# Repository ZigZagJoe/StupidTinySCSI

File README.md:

StupidTinySCSI
Derived from ZuliSCSI Pico OSHW.

This should be good but has not been 100% validated.

See below for orginal document.....

ZuluSCSI™ Pico Community Edition - Open Source Hardware
========================

This repository contains the KiCAD 7 schematic and PCB design files for the Pico-based ZuluSCSI™ SCSI to SD storage emulator, which is derived from the ZuluSCSI RP2040 board design. Firmware for ZuluSCSI is available at http://github.com/ZuluSCSI/ZuluSCSI-firmware.

This hardware design is licensed under the terms of the strongly reciprocal CERN OHL-S V2 license, which can be viewed in full at https://ohwr.org/cern_ohl_s_v2.txt and https://ohwr.org/cern_ohl_s_v2.pdf. 

ZuluSCSI™ is a registered trademark of Rabbit Hole Computing, and may not be used commercially without the express written consent of Rabbit Hole Computing. Individuals producing ZuluSCSI boards for personal use are hereby granted permission to use the ZuluSCSI trademark in a noncommercial capacity.

_Any_ use of the ZuluSCSI trademark in a **commercial** context requires prior written consent from Rabbit Hole Computing.

Firmware for ZuluSCSI is licensed under the GNU GPL Version 3, and can be found at https://github.com/zuluscsi/ZuluSCSI-firmware

Generating fabrication files
----------------------------

The component part numbers are stored in KiCAD schematic.
Manufacturing files, including assembly BOM, can be generated using [KiKit](https://github.com/yaqwsx/KiKit).

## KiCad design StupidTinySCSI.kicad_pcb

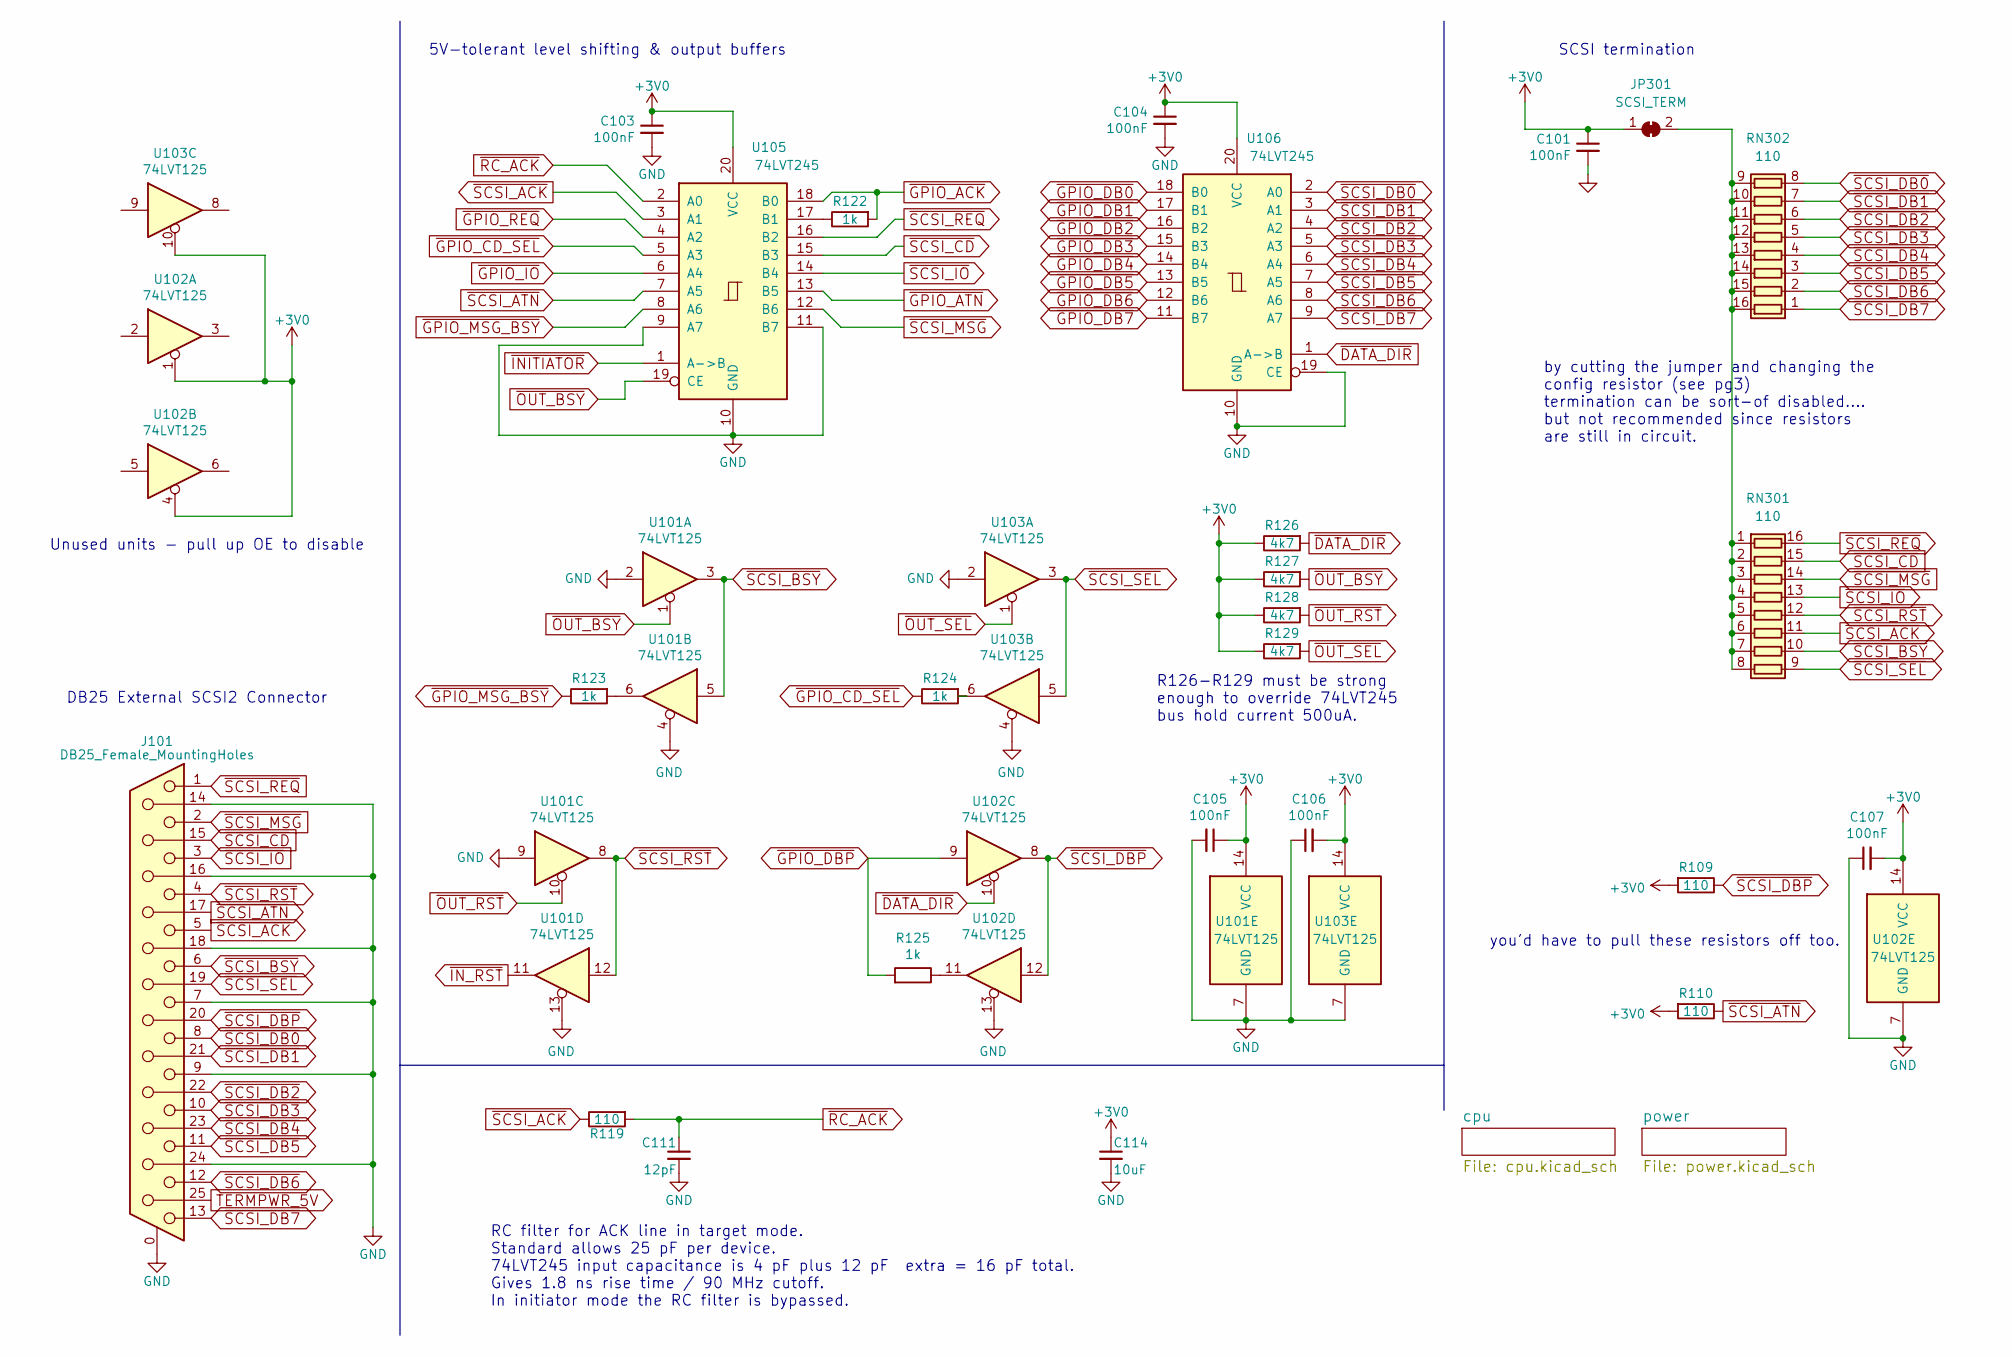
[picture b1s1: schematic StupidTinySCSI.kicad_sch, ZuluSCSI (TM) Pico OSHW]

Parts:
C101, C103, C104, C105, C106, C107: 100nF; C_0603_1608Metric; PartNumber CL10B104KB8NNWC; LCSC C14663
C111: 12pF; C_0603_1608Metric; PartNumber C0603C120J5GAC7867; LCSC C38523
C114: 10uF; C_0805_2012Metric; PartNumber CL21A106KPFNNNG; LCSC C15850
J101: DB25_Female_MountingHoles; DSUB-25_Female_Horizontal_P2.77x2.84mm_EdgePinOffset9.90mm_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; LCSC N/A
JP301: SCSI_TERM; SolderJumper-2_P1.3mm_Bridged_RoundedPad1.0x1.5mm
R109, R110, R119: 110; R_0603_1608Metric; PartNumber RC0603FR-07110RL; LCSC C22781
R122, R123, R124, R125: 1k; R_0603_1608Metric; PartNumber RC0603JR-071KL; LCSC C21190
R126, R127, R128, R129: 4k7; R_0603_1608Metric; PartNumber RC0603JR-074K7L; LCSC C23162
RN301, RN302: 110; R_Array_Convex_8x0602
U101, U102, U103: 74LVT125; SSOP_TSSOP-14_4.4x5mm_Pitch0.65mm_PCBWay-MaskClearance0.22mm; PartNumber 74LVTH125MTC; LCSC C7042
U105, U106: 74LVT245; SSOP_TSSOP-20_5.3x7.2mm_P0.65mm; PartNumber 74LVT245BBT20-13; LCSC C7057

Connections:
+3V0: C101.1, C103.1, C104.1, C105.1, C106.2, C107.2, C114.1, JP301.1 (A), R109.2, R110.2, R126.1, R127.1, R128.1, R129.1, U101.14 (VCC), U102.1, U102.4, U102.14 (VCC), U103.10, U103.14 (VCC), U105.20 (VCC), U106.20 (VCC); also elsewhere on the board
GND: C101.2, C103.2, C104.2, C105.2, C106.1, C107.1, C111.2, C114.2, J101.0 (PAD), J101.7, J101.9, J101.14, J101.16, J101.18, J101.24, U101.2, U101.4, U101.7 (GND), U101.9, U101.13, U102.7 (GND), U102.13, U103.2, U103.4, U103.7 (GND), U105.9 (A7), U105.10 (GND), U105.11 (B7), U106.10 (GND), U106.19 (CE); also elsewhere on the board
unnamed: JP301.2 (B), RN301.1 (R1.1), RN301.2 (R2.1), RN301.3 (R3.1), RN301.4 (R4.1), RN301.5 (R5.1), RN301.6 (R6.1), RN301.7 (R7.1), RN301.8 (R8.1), RN302.9 (R8.2), RN302.10 (R7.2), RN302.11 (R6.2), RN302.12 (R5.2), RN302.13 (R4.2), RN302.14 (R3.2), RN302.15 (R2.2), RN302.16 (R1.2)
unnamed: R123.2, U101.6
unnamed: R124.2, U103.6
unnamed: R125.1, U102.11
unnamed: R122.1, U105.17 (B1)
TERMPWR_5V: J101.25; also elsewhere on the board
~DATA_DIR: R126.2, U102.10, U106.1 (A->B); also elsewhere on the board
~DBGLOG: U105.4 (A2); also elsewhere on the board
~GPIO_ACK: R122.2, U105.18 (B0); also elsewhere on the board
~GPIO_ATN: U105.1 (A->B), U105.13 (B5); also elsewhere on the board
~GPIO_CD_SEL: R124.1, U105.5 (A3); also elsewhere on the board
~GPIO_DB0: U106.18 (B0); also elsewhere on the board
~GPIO_DB1: U106.17 (B1); also elsewhere on the board
~GPIO_DB2: U106.16 (B2); also elsewhere on the board
~GPIO_DB3: U106.15 (B3); also elsewhere on the board
~GPIO_DB4: U106.14 (B4); also elsewhere on the board
~GPIO_DB5: U106.13 (B5); also elsewhere on the board
~GPIO_DB6: U106.12 (B6); also elsewhere on the board
~GPIO_DB7: U106.11 (B7); also elsewhere on the board
~GPIO_DBP: R125.2, U102.9; also elsewhere on the board
~GPIO_IO: U105.6 (A4); also elsewhere on the board
~GPIO_MSG_BSY: R123.1, U105.8 (A6); also elsewhere on the board
~IN_RST: U101.11; also elsewhere on the board
~OUT_BSY: R127.2, U101.1, U105.19 (CE); also elsewhere on the board
~OUT_RST: R128.2, U101.10; also elsewhere on the board
~OUT_SEL: R129.2, U103.1; also elsewhere on the board
~RC_ACK: C111.1, R119.2, U105.2 (A0)
~SCSI_ACK: J101.5, R119.1, RN301.11 (R6.2), U105.3 (A1)
~SCSI_ATN: J101.17, R110.1, U105.7 (A5)
~SCSI_BSY: J101.6, RN301.10 (R7.2), U101.3, U101.5
~SCSI_CD: J101.15, RN301.15 (R2.2), U105.15 (B3)
~SCSI_DB0: J101.8, RN302.8 (R8.1), U106.2 (A0)
~SCSI_DB1: J101.21, RN302.7 (R7.1), U106.3 (A1)
~SCSI_DB2: J101.22, RN302.6 (R6.1), U106.4 (A2)
~SCSI_DB3: J101.10, RN302.5 (R5.1), U106.5 (A3)
~SCSI_DB4: J101.23, RN302.4 (R4.1), U106.6 (A4)
~SCSI_DB5: J101.11, RN302.3 (R3.1), U106.7 (A5)
~SCSI_DB6: J101.12, RN302.2 (R2.1), U106.8 (A6)
~SCSI_DB7: J101.13, RN302.1 (R1.1), U106.9 (A7)
~SCSI_DBP: J101.20, R109.1, U102.8, U102.12
~SCSI_IO: J101.3, RN301.13 (R4.2), U105.14 (B4)
~SCSI_MSG: J101.2, RN301.14 (R3.2), U105.12 (B6)
~SCSI_REQ: J101.1, RN301.16 (R1.2), U105.16 (B2)
~SCSI_RST: J101.4, RN301.12 (R5.2), U101.8, U101.12
~SCSI_SEL: J101.19, RN301.9 (R8.2), U103.3, U103.5

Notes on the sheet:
SCSI termination
R126-R129 must be strong enough to override 74LVT245 bus hold current 500uA.
5V-tolerant level shifting & output buffers
you'd have to pull these resistors off too.
by cutting the jumper and changing the config resistor (see pg3) termination can be sort-of disabled.... but not recommended since resistors are still in circuit.
Unused units - pull up OE to disable
DB25 External SCSI2 Connector
RC filter for ACK line in target mode. Standard allows 25 pF per device. 74LVT245 input capacitance is 4 pF plus 12 pF extra = 16 pF total. Gives 1.8 ns rise time / 90 MHz cutoff. In initiator mode the RC filter is bypassed.

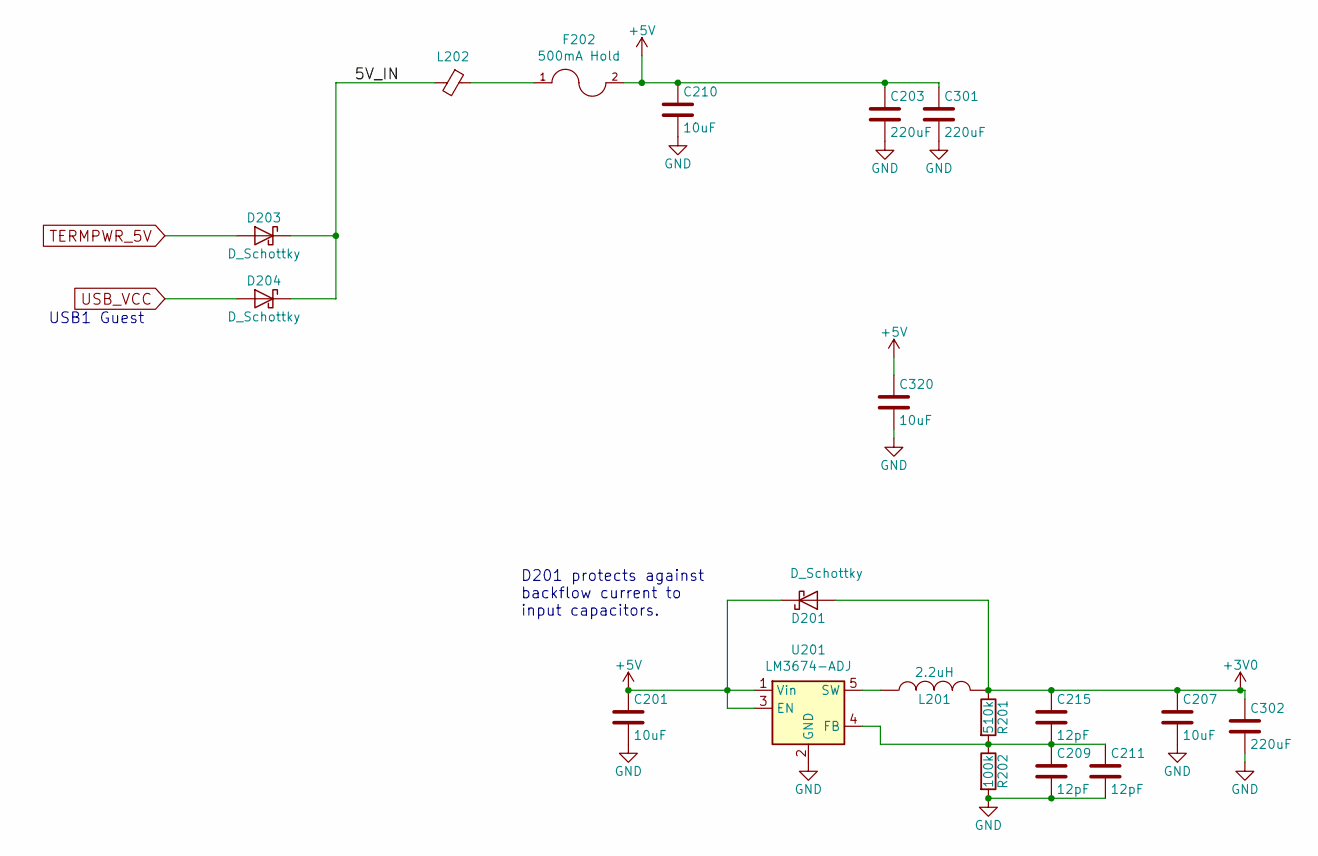
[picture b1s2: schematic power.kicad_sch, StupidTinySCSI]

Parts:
C201, C207, C210, C320: 10uF; C_0805_2012Metric; PartNumber CL21A106KPFNNNG; LCSC C15850
C203, C301, C302: 220uF; CP_EIA-6032-15_Kemet-U_Pad2.25x2.35mm_HandSolder; PartNumber TAJC227K010RNJ; digikey 478-4774-1-ND
C209, C211, C215: 12pF; C_0603_1608Metric; PartNumber C0603C120J5GAC7867; LCSC C38523
D201, D203, D204: D_Schottky; D_SOD-123; PartNumber MBRX120LF-TP; LCSC C8598
F202: 500mA Hold; Fuse_1206_3216Metric; PartNumber 0ZCJ0050FF2G; LCSC C369160
L201: 2.2uH; Inductor_1008; PartNumber DFE252012P-2R2M=P2; LCSC C86092
L202: Ferrite_Bead_Small; L_0603_1608Metric; PartNumber PE-0603FB601ST; LCSC C1002
R201: 510k; R_0603_1608Metric; PartNumber RC0603FR-07510KL; LCSC C23192
R202: 100k; R_0603_1608Metric; PartNumber RC0603FR-07100KL; LCSC C25803
U201: LM3674-ADJ; TSOT-23-5; PartNumber LM3674MFX-ADJ/NOPB; LCSC C52027

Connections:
+3V0: C207.1, C215.1, C302.1, D201.2 (A), L201.2, R201.1; also elsewhere on the board
+5V: C201.1, C203.1, C210.1, C301.1, D201.1 (K), F202.2, U201.1 (Vin), U201.3 (EN); also elsewhere on the board
/power/5V_IN: D203.1 (K), D204.1 (K), L202.2
GND: C201.2, C203.2, C207.2, C209.2, C210.2, C211.2, C301.2, C302.2, R202.2, U201.2 (GND); also elsewhere on the board
unnamed: F202.1, L202.1
unnamed: C209.1, C211.1, C215.2, R201.2, R202.1, U201.4 (FB)
unnamed: L201.1, U201.5 (SW)
TERMPWR_5V: D203.2 (A); also elsewhere on the board
USB_VCC: D204.2 (A); also elsewhere on the board

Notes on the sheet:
USB1 Guest
D201 protects against backflow current to input capacitors.

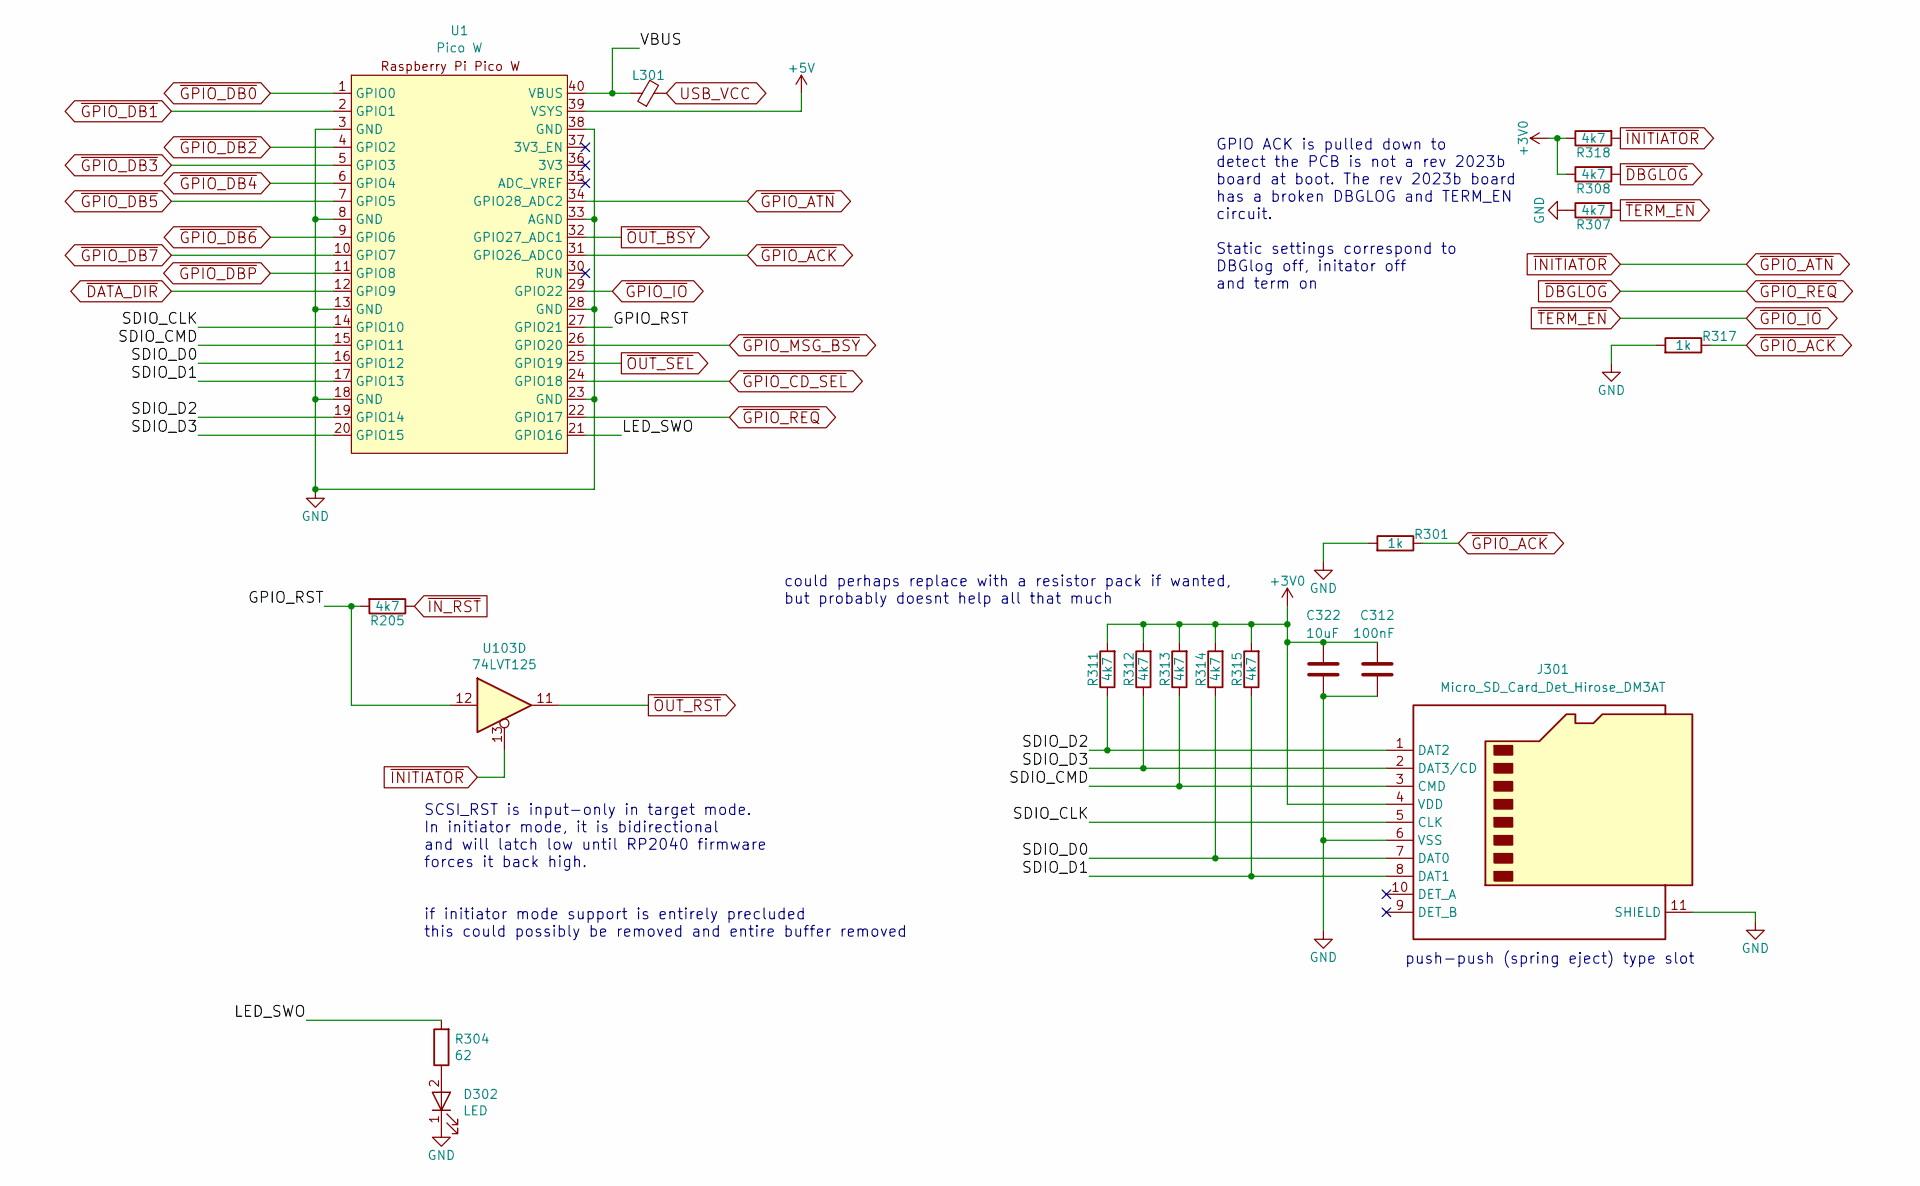
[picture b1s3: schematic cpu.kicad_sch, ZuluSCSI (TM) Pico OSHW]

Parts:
C312: 100nF; C_0603_1608Metric; PartNumber CL10B104KB8NNWC; LCSC C14663
C322: 10uF; C_0805_2012Metric; PartNumber CL21A106KPFNNNG; LCSC C15850
D302: LED; LED_0805_2012Metric; PartNumber LY R976-PS-36; LCSC C434435
J301: Micro_SD_Card_Det_Hirose_DM3AT; microSD_HC_Hirose_DM3AT-SF-PEJM5
L301: Ferrite_Bead_Small; L_0603_1608Metric; PartNumber PE-0603FB601ST; LCSC C1002
R205, R311, R312, R313, R314, R315: 4k7; R_0603_1608Metric; PartNumber RC0603JR-074K7L; LCSC C23162
R301, R317: 1k; R_0603_1608Metric; PartNumber RC0603JR-071KL; LCSC C21190
R304: 62; R_0603_1608Metric; PartNumber RC0603FR-0762RL; LCSC C25252
R307, R308, R318: 4k7; R_0603_1608Metric
U1: Pico W; RPi_Pico_WH_headers; LCSC N/A
U103: 74LVT125; SSOP_TSSOP-14_4.4x5mm_Pitch0.65mm_PCBWay-MaskClearance0.22mm; PartNumber 74LVTH125MTC; LCSC C7042

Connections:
+3V0: C312.2, C322.2, J301.4 (VDD), R308.1, R311.2, R312.2, R313.2, R314.2, R315.2, R318.1; also elsewhere on the board
+5V: U1.39 (VSYS); also elsewhere on the board
/cpu/GPIO_RST: R205.2, U1.27 (GPIO21), U103.12
/cpu/LED_SWO: R304.2, U1.21 (GPIO16)
/cpu/SDIO_CLK: J301.5 (CLK), U1.14 (GPIO10)
/cpu/SDIO_CMD: J301.3 (CMD), R313.1, U1.15 (GPIO11)
/cpu/SDIO_D0: J301.7 (DAT0), R314.1, U1.16 (GPIO12)
/cpu/SDIO_D1: J301.8 (DAT1), R315.1, U1.17 (GPIO13)
/cpu/SDIO_D2: J301.1 (DAT2), R311.1, U1.19 (GPIO14)
/cpu/SDIO_D3: J301.2 (DAT3/CD), R312.1, U1.20 (GPIO15)
/cpu/VBUS: L301.1, U1.40 (VBUS)
GND: C312.1, C322.1, D302.1 (K), J301.6 (VSS), J301.11 (SHIELD), R301.2, R307.1, R317.2, U1.3 (GND), U1.8 (GND), U1.13 (GND), U1.18 (GND), U1.23 (GND), U1.28 (GND), U1.33 (AGND), U1.38 (GND); also elsewhere on the board
unnamed: D302.2 (A), R304.1
USB_VCC: L301.2; also elsewhere on the board
~DATA_DIR: U1.12 (GPIO9); also elsewhere on the board
~DBGLOG: R308.2, U1.22 (GPIO17); also elsewhere on the board
~GPIO_ACK: R301.1, R317.1, U1.31 (GPIO26_ADC0); also elsewhere on the board
~GPIO_ATN: R318.2, U1.34 (GPIO28_ADC2), U103.13; also elsewhere on the board
~GPIO_CD_SEL: U1.24 (GPIO18); also elsewhere on the board
~GPIO_DB0: U1.1 (GPIO0); also elsewhere on the board
~GPIO_DB1: U1.2 (GPIO1); also elsewhere on the board
~GPIO_DB2: U1.4 (GPIO2); also elsewhere on the board
~GPIO_DB3: U1.5 (GPIO3); also elsewhere on the board
~GPIO_DB4: U1.6 (GPIO4); also elsewhere on the board
~GPIO_DB5: U1.7 (GPIO5); also elsewhere on the board
~GPIO_DB6: U1.9 (GPIO6); also elsewhere on the board
~GPIO_DB7: U1.10 (GPIO7); also elsewhere on the board
~GPIO_DBP: U1.11 (GPIO8); also elsewhere on the board
~GPIO_IO: R307.2, U1.29 (GPIO22); also elsewhere on the board
~GPIO_MSG_BSY: U1.26 (GPIO20); also elsewhere on the board
~IN_RST: R205.1; also elsewhere on the board
~OUT_BSY: U1.32 (GPIO27_ADC1); also elsewhere on the board
~OUT_RST: U103.11; also elsewhere on the board
~OUT_SEL: U1.25 (GPIO19); also elsewhere on the board

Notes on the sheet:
GPIO ACK is pulled down to detect the PCB is not a rev 2023b board at boot. The rev 2023b board has a broken DBGLOG and TERM_EN circuit. Static settings correspond to DBGlog off, initator off and term on
could perhaps replace with a resistor pack if wanted, but probably doesnt help all that much
push-push (spring eject) type slot
SCSI_RST is input-only in target mode. In initiator mode, it is bidirectional and will latch low until RP2040 firmware forces it back high. if initiator mode support is entirely precluded this could possibly be removed and entire buffer removed

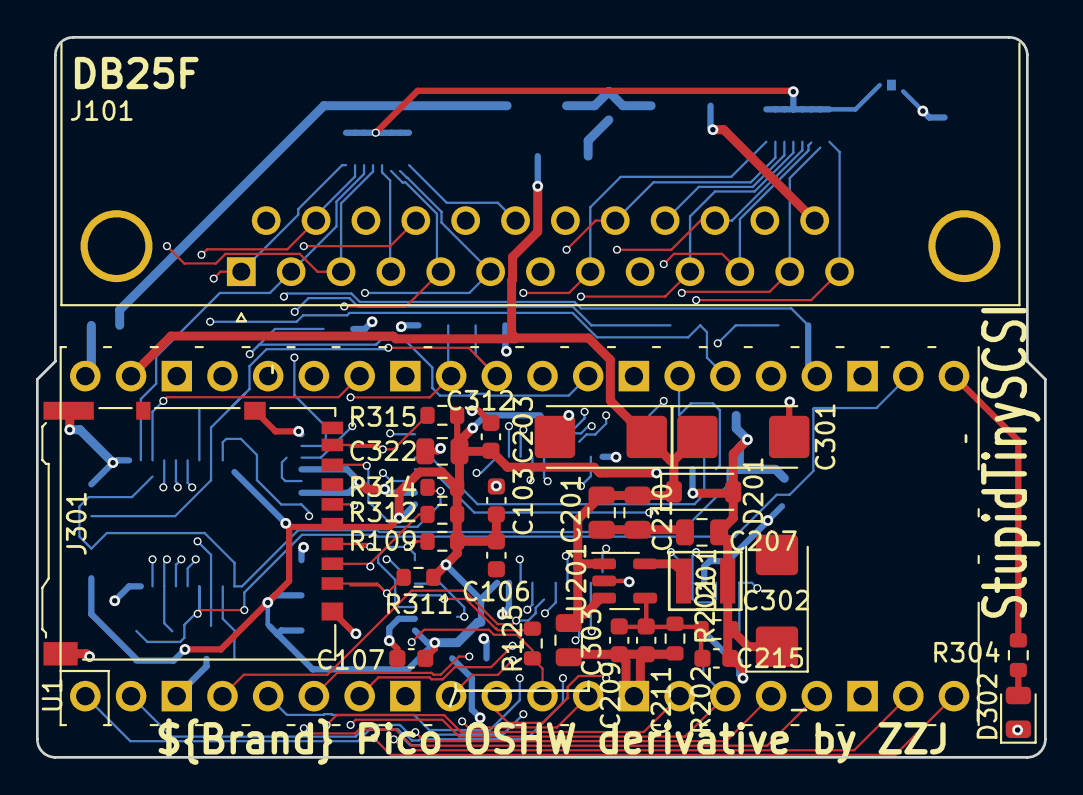
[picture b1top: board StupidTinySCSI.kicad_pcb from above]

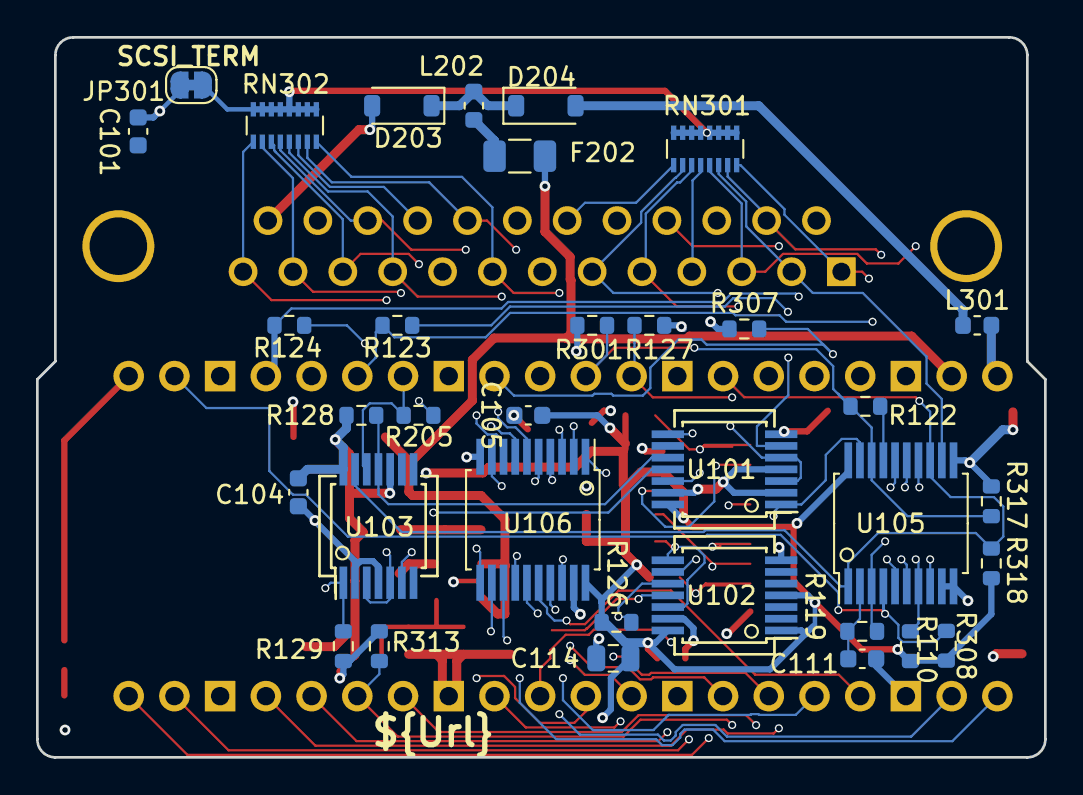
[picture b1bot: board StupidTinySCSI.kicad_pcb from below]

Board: 4 copper layers, 56.0 x 40.0 mm, 65 parts (34 on the bottom side), 63 nets.

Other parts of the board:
C303: 10uF; C_0805_2012Metric

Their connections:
+5V: C303.1; also elsewhere on the board
GND: C303.2; also elsewhere on the board

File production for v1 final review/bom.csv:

Designator,Footprint,Quantity,Value,LCSC Part #
"C101, C103, C104, C105, C106, C107, C312",0603,7,100nF,C14663
"C111, C209, C211, C215",0603,4,12pF,C38523
"C114, C201, C207, C210, C303, C322",0805,6,10uF,C15850
"C203, C301, C302",CP_EIA-6032-15_Kemet-U_Pad2.25x2.35mm_HandSolder,3,220uF,
"D201, D203, D204",D_SOD-123,3,D_Schottky,C8598
D302,0805,1,LED,C434435
F202,1206,1,500mA Hold,C369160
J101,DSUB-25_Female_Horizontal_P2.77x2.84mm_EdgePinOffset9.90mm_Housed_MountingHolesOffset11.32mm,1,DB25_Female_MountingHoles,N/A
J301,microSD_HC_Hirose_DM3AT-SF-PEJM5,1,Micro_SD_Card_Det_Hirose_DM3AT,
JP301,SolderJumper-2_P1.3mm_Bridged_RoundedPad1.0x1.5mm,1,SCSI_TERM,
L201,Inductor_1008,1,2.2uH,C86092
"L202, L301",0603,2,Ferrite_Bead_Small,C1002
"R109, R110, R119",0603,3,110,C22781
"R122, R123, R124, R125, R301, R317",0603,6,1k,C21190
"R126, R127, R128, R129, R205, R307, R308, R311, R312, R313, R314, R315, R318",0603,13,4k7,C23162
R201,0603,1,510k,C23192
R202,0603,1,100k,C25803
R304,0603,1,62,C25252
"RN301, RN302",R_Array_Convex_8x0602,2,110,
U1,RPi_Pico_WH_headers,1,Pico W,N/A
"U101, U102, U103",SSOP_TSSOP-14_4.4x5mm_Pitch0.65mm_PCBWay-MaskClearance0.22mm,3,74LVT125,C7042
"U105, U106",SSOP_TSSOP-20_5.3x7.2mm_P0.65mm,2,74LVT245,C7057
U201,TSOT-23-5,1,LM3674-ADJ,C52027

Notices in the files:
parts and their libraries:
Copyright: ©2023 Rabbit Hole Computing LLC
License: Licensed under CERN Open Hardware License Strongly Reciprocal Version 2
LicenseURL: https://spdx.org/licenses/CERN-OHL-S-2.0.html
